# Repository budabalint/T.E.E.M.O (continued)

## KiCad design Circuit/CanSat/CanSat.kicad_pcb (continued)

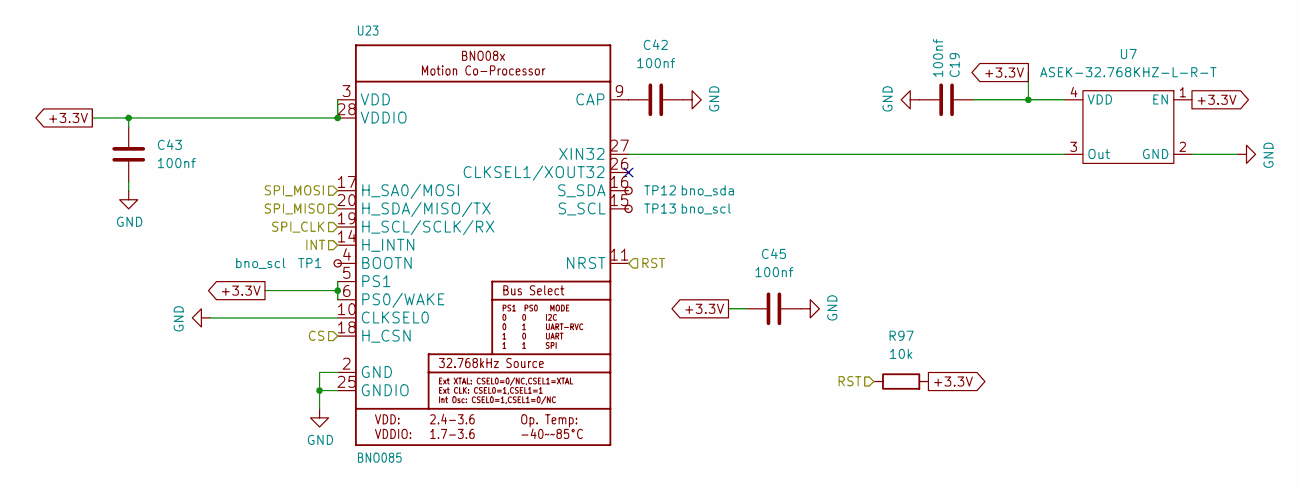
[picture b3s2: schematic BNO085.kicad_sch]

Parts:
C19, C42, C43, C45: 100nf; C_0805_2012Metric
R97: 10k; R_0805_2012Metric
TP1, TP13: bno_scl; TestPoint_Pad_D1.5mm
TP12: bno_sda; TestPoint_Pad_D1.5mm
U7: ASEK-32.768KHZ-L-R-T; Crystal_SMD_3225-4Pin_3.2x2.5mm
U23: BNO085; LGA-28_5.2x3.8mm_P0.5mm

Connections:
+3.3V: C19.1, C43.1, C45.1, R97.2, U7.1 (EN), U7.4 (VDD), U23.3 (VDD), U23.5 (PS1), U23.6 (PS0/WAKE), U23.28 (VDDIO); also elsewhere on the board
/SPI_CLK: U23.19 (H_SCL/SCLK/RX); also elsewhere on the board
/SPI_MISO: U23.20 (H_SDA/MISO/TX); also elsewhere on the board
/SPI_MOSI: U23.17 (H_SA0/MOSI); also elsewhere on the board
/bno_cs: U23.18 (H_CSN); also elsewhere on the board
/bno_int: U23.14 (H_INTN); also elsewhere on the board
/bno_rst: R97.1, U23.11 (NRST); also elsewhere on the board
GND: C19.2, C42.2, C43.2, C45.2, U7.2 (GND), U23.2 (GND), U23.10 (CLKSEL0), U23.25 (GNDIO); also elsewhere on the board
unnamed 75: TP1.1, U23.4 (BOOTN); also elsewhere on the board
unnamed: C42.1, U23.9 (CAP)
unnamed 77: TP13.1, U23.15 (S_SCL); also elsewhere on the board
unnamed 78: TP12.1, U23.16 (S_SDA); also elsewhere on the board
unnamed: U7.3 (Out), U23.27 (XIN32)

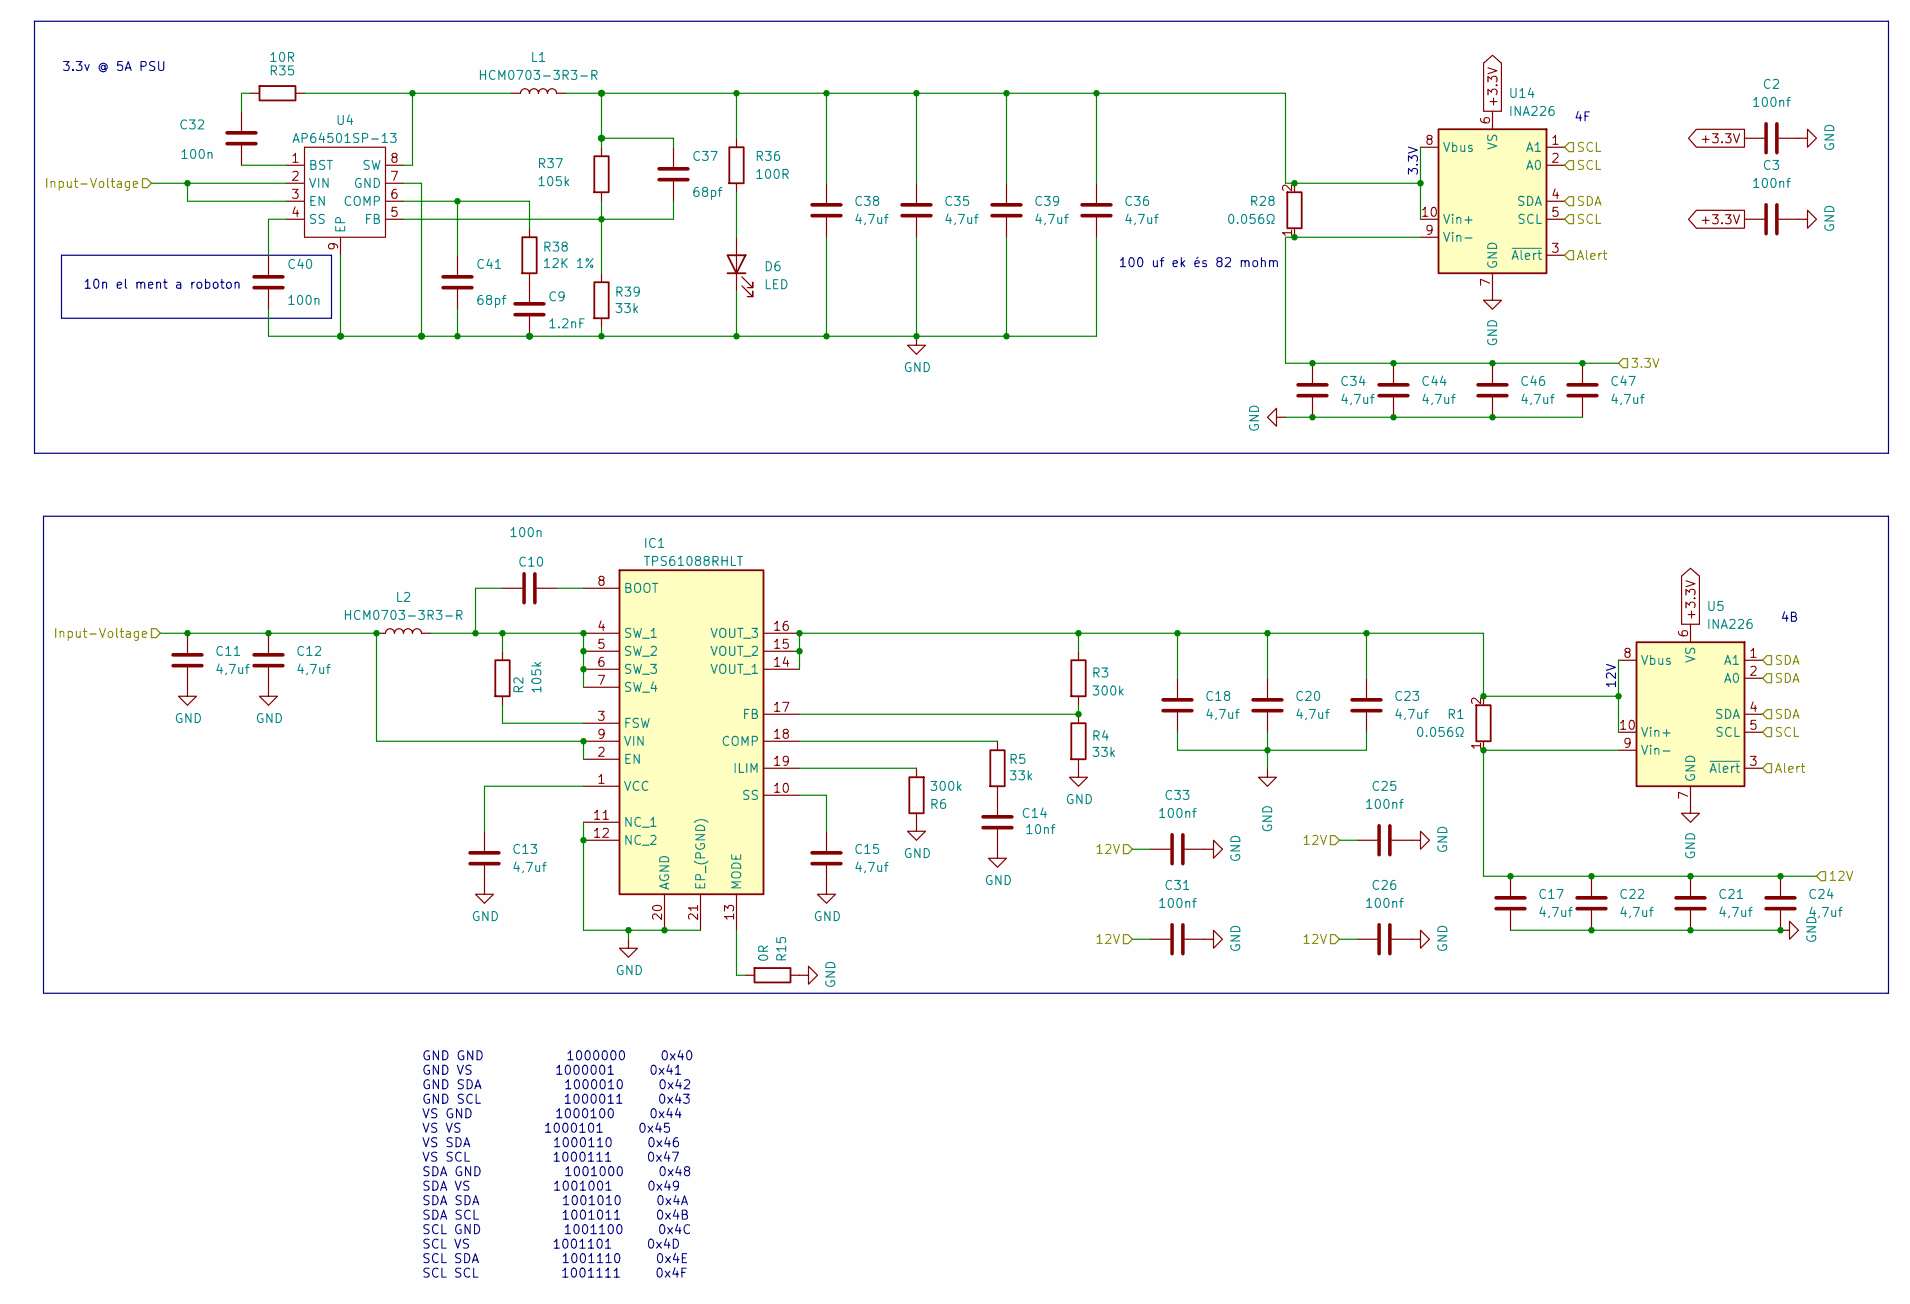
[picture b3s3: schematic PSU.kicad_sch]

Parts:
C2, C3, C25, C26, C31, C33: 100nf; C_0805_2012Metric
C9: 1.2nF; C_0805_2012Metric
C10, C32, C40: 100n; C_0805_2012Metric
C11, C12, C13, C15, C17, C18, C20, C21, C22, C23, C24, C34, C35, C36, C38, C39, C44, C46, C47: 4,7uf; C_0805_2012Metric
C14: 10nf; C_0805_2012Metric
C37, C41: 68pf; C_0805_2012Metric
D6: LED; D_1206_3216Metric
IC1: TPS61088RHLT; BQ24031IRHLRQ1; Manufacturer_Part_Number TPS61088RHLT; Mouser Part Number 595-TPS61088RHLT
L1, L2: HCM0703-3R3-R; HCM1A0805
R1, R28: 0.056Ω; R_1206_3216Metric
R2, R37: 105k; R_0805_2012Metric
R3, R6: 300k; R_0805_2012Metric
R4, R5, R39: 33k; R_0805_2012Metric
R15: 0R; R_0805_2012Metric
R35: 10R; R_0805_2012Metric
R36: 100R; R_0805_2012Metric
R38: 12K 1%; R_0805_2012Metric
U4: AP64501SP-13; SOIC-8-1EP_3.9x4.9mm_P1.27mm_EP2.95x4.9mm_Mask2.71x3.4mm_Th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
U5, U14: INA226; VSSOP-10_3x3mm_P0.5mm

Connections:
+3.3V: C2.1, C3.1, C34.1, C44.1, C46.1, C47.1, R28.1, U5.6 (VS), U14.6 (VS), U14.9 (Vin-); also elsewhere on the board
+12V: C17.1, C21.1, C22.1, C24.1, C25.1, C26.1, C31.1, C33.1, R1.1, U5.9 (Vin-); also elsewhere on the board
/Alert: U5.3 (~Alert), U14.3 (~Alert); also elsewhere on the board
/PSU/Input-Voltage: C11.1, C12.1, IC1.2 (EN), IC1.9 (VIN), L2.2, U4.2 (VIN), U4.3 (EN); also elsewhere on the board
/Slow-SCL: U5.5 (SCL), U14.1 (A1), U14.2 (A0), U14.5 (SCL); also elsewhere on the board
/Slow-SDA: U5.1 (A1), U5.2 (A0), U5.4 (SDA), U14.4 (SDA); also elsewhere on the board
GND: C2.2, C3.2, C9.2, C11.2, C12.2, C13.2, C14.2, C15.2, C17.2, C18.2, C20.2, C21.2, C22.2, C23.2, C24.2, C25.2, C26.2, C31.2, C33.2, C34.2, C35.2, C36.2, C38.2, C39.2, C40.2, C41.2, C44.2, C46.2, C47.2, D6.1 (K), IC1.11 (NC_1), IC1.12 (NC_2), IC1.20 (AGND), IC1.21 (EP_(PGND)), R4.2, R6.1, R15.1, R39.2, U4.7 (GND), U4.9 (EP), U5.7 (GND), U14.7 (GND); also elsewhere on the board
unnamed: C9.1, R38.2
unnamed: C14.1, R5.2
unnamed: C32.1, R35.2
unnamed: D6.2 (A), R36.2
unnamed: C10.2, IC1.8 (BOOT)
unnamed: IC1.18 (COMP), R5.1
unnamed: IC1.17 (FB), R3.2, R4.1
unnamed: IC1.3 (FSW), R2.2
unnamed: IC1.19 (ILIM), R6.2
unnamed: IC1.13 (MODE), R15.2
unnamed: C15.1, IC1.10 (SS)
unnamed: C10.1, IC1.4 (SW_1), IC1.5 (SW_2), IC1.6 (SW_3), IC1.7 (SW_4), L2.1, R2.1
unnamed: C13.1, IC1.1 (VCC)
unnamed: C18.1, C20.1, C23.1, IC1.14 (VOUT_1), IC1.15 (VOUT_2), IC1.16 (VOUT_3), R1.2, R3.1, U5.8 (Vbus), U5.10 (Vin+)
unnamed: C32.2, U4.1 (BST)
unnamed: C41.1, R38.1, U4.6 (COMP)
unnamed: C37.2, R37.2, R39.1, U4.5 (FB)
unnamed: C40.1, U4.4 (SS)
unnamed: L1.1, R35.1, U4.8 (SW)
unnamed: C35.1, C36.1, C37.1, C38.1, C39.1, L1.2, R28.2, R36.1, R37.1, U14.8 (Vbus), U14.10 (Vin+)

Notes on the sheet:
12V
100 uf ek és 82 mohm
10n el ment a roboton
3.3v @ 5A PSU
3.3V
GND GND 1000000 0x40 GND VS 1000001 0x41 GND SDA 1000010 0x42 GND SCL 1000011 0x43 VS GND 1000100 0x44 VS VS 1000101 0x45 VS SDA 1000110 0x46 VS SCL 1000111 0x47 SDA GND 1001000 0x48 SDA VS 1001001 0x49 SDA SDA 1001010 0x4A SDA SCL 1001011 0x4B SCL GND 1001100 0x4C SCL VS 1001101 0x4D SCL SDA 10011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

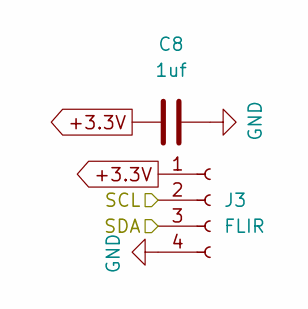
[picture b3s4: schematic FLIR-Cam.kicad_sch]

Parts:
C8: 1uf; C_0805_2012Metric
J3: FLIR; JST_PH_B4B-PH-K_1x04_P2.00mm_Vertical

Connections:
+3.3V: C8.1, J3.1; also elsewhere on the board
/Fast-SCL: J3.2; also elsewhere on the board
/Fast-SDA: J3.3; also elsewhere on the board
GND: C8.2, J3.4; also elsewhere on the board

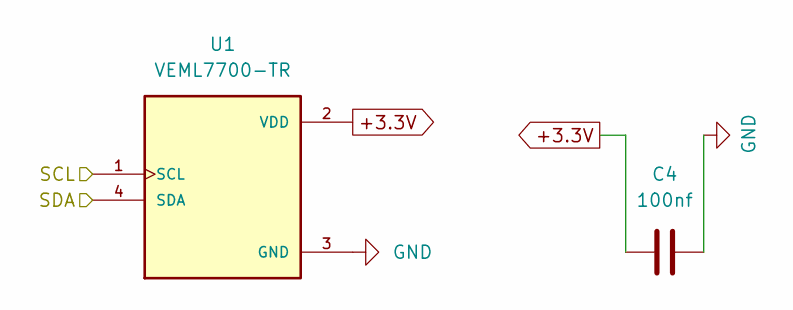
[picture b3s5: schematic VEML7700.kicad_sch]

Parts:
C4: 100nf; C_0805_2012Metric
U1: VEML7700-TR; XDCR_VEML7700-TR; PARTREV 1.6

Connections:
+3.3V: C4.1, U1.2 (VDD); also elsewhere on the board
/Slow-SCL: U1.1 (SCL); also elsewhere on the board
/Slow-SDA: U1.4 (SDA); also elsewhere on the board
GND: C4.2, U1.3 (GND); also elsewhere on the board

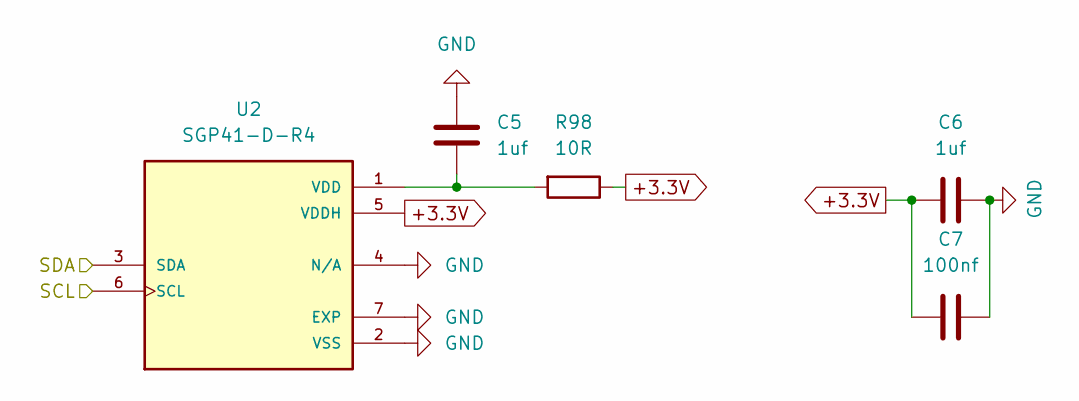
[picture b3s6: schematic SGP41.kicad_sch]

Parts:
C5, C6: 1uf; C_0805_2012Metric
C7: 100nf; C_0805_2012Metric
R98: 10R; R_0805_2012Metric
U2: SGP41-D-R4; XDCR_SGP41-D-R4; PARTREV 1.0

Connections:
+3.3V: C6.1, C7.1, R98.1, U2.5 (VDDH); also elsewhere on the board
/Slow-SCL: U2.6 (SCL); also elsewhere on the board
/Slow-SDA: U2.3 (SDA); also elsewhere on the board
GND: C5.2, C6.2, C7.2, U2.2 (VSS), U2.4 (N/A), U2.7 (EXP); also elsewhere on the board
unnamed: C5.1, R98.2, U2.1 (VDD)

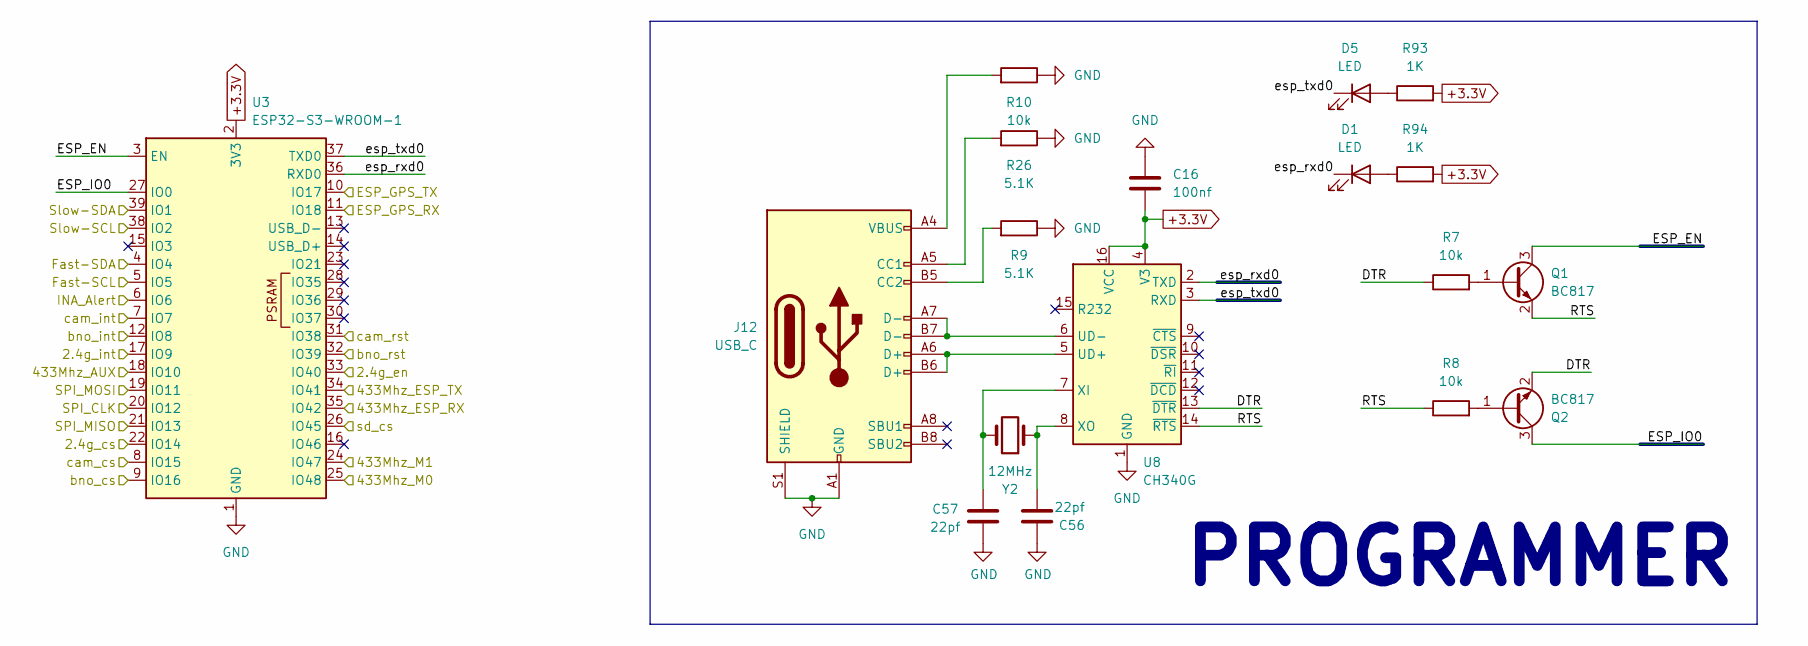
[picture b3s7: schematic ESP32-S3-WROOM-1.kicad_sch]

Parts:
C16: 100nf; C_0805_2012Metric
C56, C57: 22pf; C_0805_2012Metric
D1, D5: LED; D_1206_3216Metric
J12: USB_C; USB_C_Receptacle_Palconn_UTC16-G
Q1, Q2: BC817; SOT-23
R7, R8, R10: 10k; R_0805_2012Metric
R9, R26: 5.1K; R_0805_2012Metric
R93, R94: 1K; R_0805_2012Metric
U3: ESP32-S3-WROOM-1
U8: CH340G; SOIC-16_3.9x9.9mm_P1.27mm
Y2: 12MHz; Crystal_SMD_HC49-SD

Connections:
+3.3V: C16.2, R93.2, R94.2, U3.2 (3V3), U8.4 (V3), U8.16 (VCC); also elsewhere on the board
/2.4g_cs: U3.22 (IO14); also elsewhere on the board
/2.4g_en: U3.33 (IO40); also elsewhere on the board
/2.4g_int: U3.17 (IO9); also elsewhere on the board
/AUX: U3.18 (IO10); also elsewhere on the board
/Alert: U3.6 (IO6); also elsewhere on the board
/ESP32-S3-WROOM-1/DTR: Q2.2 (E), R7.1, U8.13 (~DTR)
/ESP32-S3-WROOM-1/ESP_EN: Q1.3 (C), U3.3 (EN)
/ESP32-S3-WROOM-1/ESP_IO0: Q2.3 (C), U3.27 (IO0)
/ESP32-S3-WROOM-1/RTS: Q1.2 (E), R8.1, U8.14 (~RTS)
/ESP32-S3-WROOM-1/esp_rxd0: D1.1 (K), U3.36 (RXD0), U8.2 (TXD)
/ESP32-S3-WROOM-1/esp_txd0: D5.1 (K), U3.37 (TXD0), U8.3 (RXD)
/Fast-SCL: U3.5 (IO5); also elsewhere on the board
/Fast-SDA: U3.4 (IO4); also elsewhere on the board
/GPS_RX: U3.10 (IO17); also elsewhere on the board
/GPS_TX: U3.11 (IO18); also elsewhere on the board
/M0: U3.25 (IO48); also elsewhere on the board
/M1: U3.24 (IO47); also elsewhere on the board
/RX: U3.34 (IO41); also elsewhere on the board
/SPI_CLK: U3.20 (IO12); also elsewhere on the board
/SPI_MISO: U3.21 (IO13); also elsewhere on the board
/SPI_MOSI: U3.19 (IO11); also elsewhere on the board
/Slow-SCL: U3.38 (IO2); also elsewhere on the board
/Slow-SDA: U3.39 (IO1); also elsewhere on the board
/TX: U3.35 (IO42); also elsewhere on the board
/bno_cs: U3.9 (IO16); also elsewhere on the board
/bno_int: U3.12 (IO8); also elsewhere on the board
/bno_rst: U3.32 (IO39); also elsewhere on the board
/cam_cs: U3.8 (IO15); also elsewhere on the board
/cam_int: U3.7 (IO7); also elsewhere on the board
/cam_rst: U3.31 (IO38); also elsewhere on the board
/sd_cs: U3.26 (IO45); also elsewhere on the board
GND: C16.1, C56.2, C57.2, J12.A1 (GND), J12.A12 (GND), J12.B1 (GND), J12.B12 (GND), J12.S1 (SHIELD), R9.1, R10.1, R26.1, U3.1 (GND), U3.40 (GND), U3.41 (GND), U8.1 (GND); also elsewhere on the board
unnamed: D1.2 (A), R94.1
unnamed: D5.2 (A), R93.1
unnamed: J12.A5 (CC1), R26.2
unnamed: J12.B5 (CC2), R9.2
unnamed: J12.A4 (VBUS), J12.A9 (VBUS), J12.B4 (VBUS), J12.B9 (VBUS), R10.2
unnamed: Q1.1 (B), R7.2
unnamed: Q2.1 (B), R8.2
unnamed: J12.A6 (D+), J12.B6 (D+), U8.5 (UD+)
unnamed: J12.A7 (D-), J12.B7 (D-), U8.6 (UD-)
unnamed: C57.1, U8.7 (XI), Y2.2
unnamed: C56.1, U8.8 (XO), Y2.1

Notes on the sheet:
PROGRAMMER

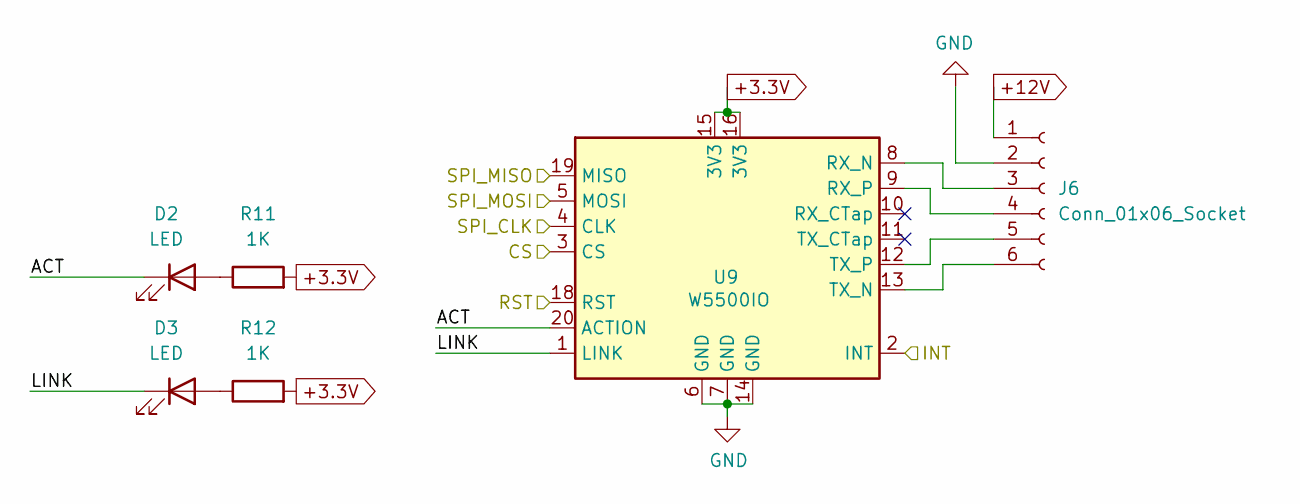
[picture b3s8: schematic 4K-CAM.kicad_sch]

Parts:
D2, D3: LED; D_1206_3216Metric
J6: Conn_01x06_Socket; JST_PH_B6B-PH-K_1x06_P2.00mm_Vertical
R11, R12: 1K; R_0805_2012Metric
U9: W5500IO; W5500-io

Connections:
+3.3V: R11.2, R12.2, U9.15 (3V3), U9.16 (3V3); also elsewhere on the board
+12V: J6.1; also elsewhere on the board
/4K-CAM/ACT: D2.1 (K), U9.20 (ACTION)
/4K-CAM/LINK: D3.1 (K), U9.1 (LINK)
/SPI_CLK: U9.4 (CLK); also elsewhere on the board
/SPI_MISO: U9.19 (MISO); also elsewhere on the board
/SPI_MOSI: U9.5 (MOSI); also elsewhere on the board
/cam_cs: U9.3 (CS); also elsewhere on the board
/cam_int: U9.2 (INT); also elsewhere on the board
/cam_rst: U9.18 (RST); also elsewhere on the board
GND: J6.2, U9.6 (GND), U9.7 (GND), U9.14 (GND); also elsewhere on the board
unnamed: D2.2 (A), R11.1
unnamed: D3.2 (A), R12.1
unnamed: J6.3, U9.8 (RX_N)
unnamed: J6.4, U9.9 (RX_P)
unnamed: J6.5, U9.12 (TX_P)
unnamed: J6.6, U9.13 (TX_N)

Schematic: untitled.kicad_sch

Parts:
C1: 100nf; C_0805_2012Metric
U21: BME280; Bosch_LGA-8_2.5x2.5mm_P0.65mm_ClockwisePinNumbering

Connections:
+3.3V: C1.1, U21.2 (CSB), U21.5 (SDO), U21.6 (VDDIO), U21.8 (VDD); also elsewhere on the board
/Slow-SCL: U21.4 (SCK); also elsewhere on the board
/Slow-SDA: U21.3 (SDI); also elsewhere on the board
GND: C1.2, U21.1 (GND), U21.7 (GND); also elsewhere on the board

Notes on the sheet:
0x77 @ VDD 0x76 @ GND

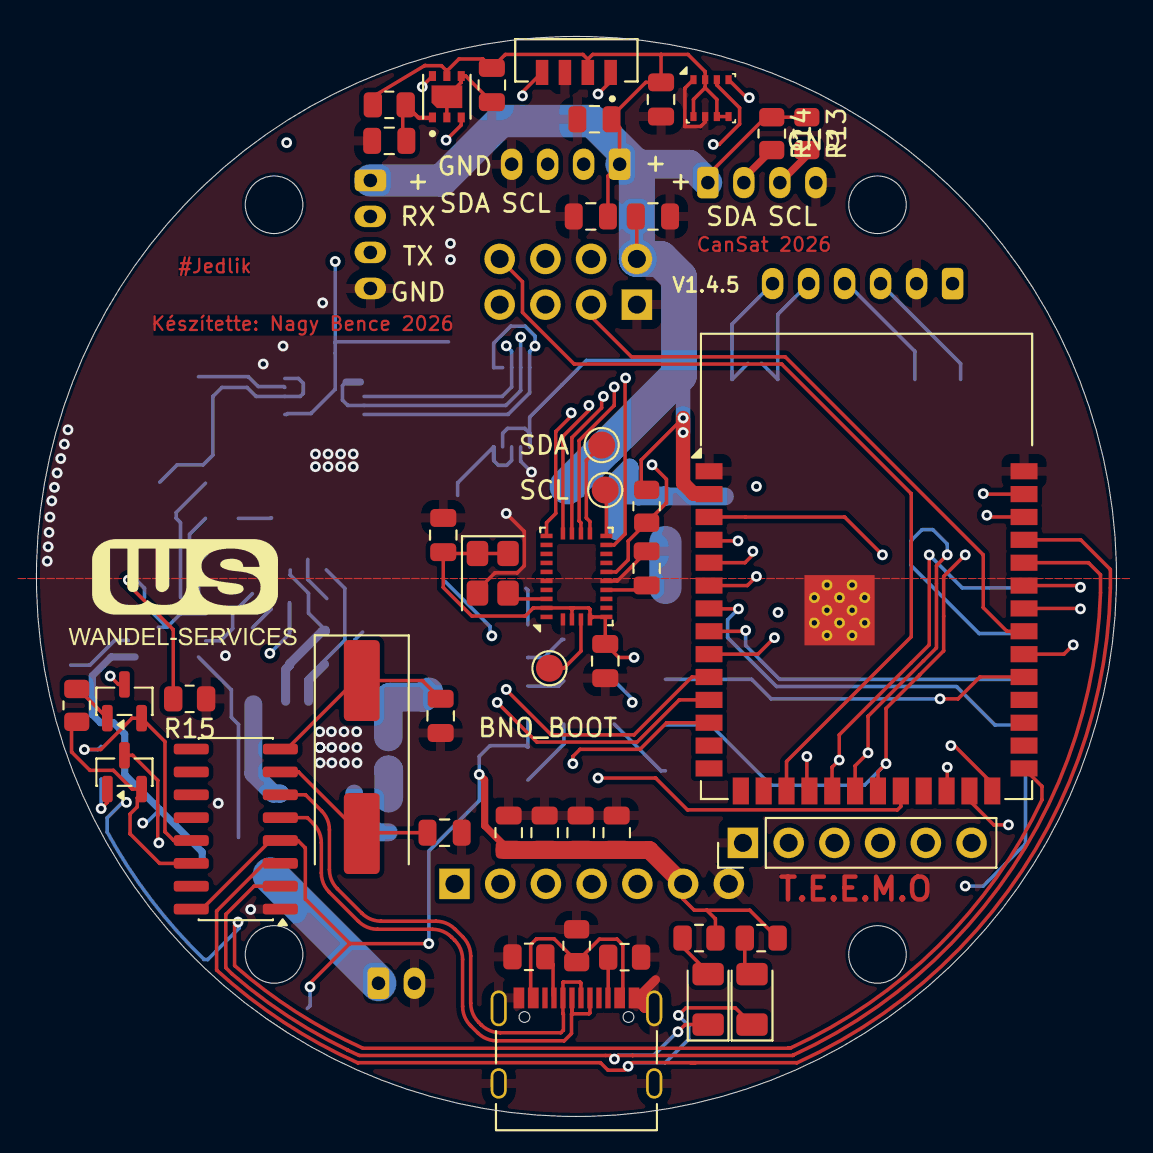
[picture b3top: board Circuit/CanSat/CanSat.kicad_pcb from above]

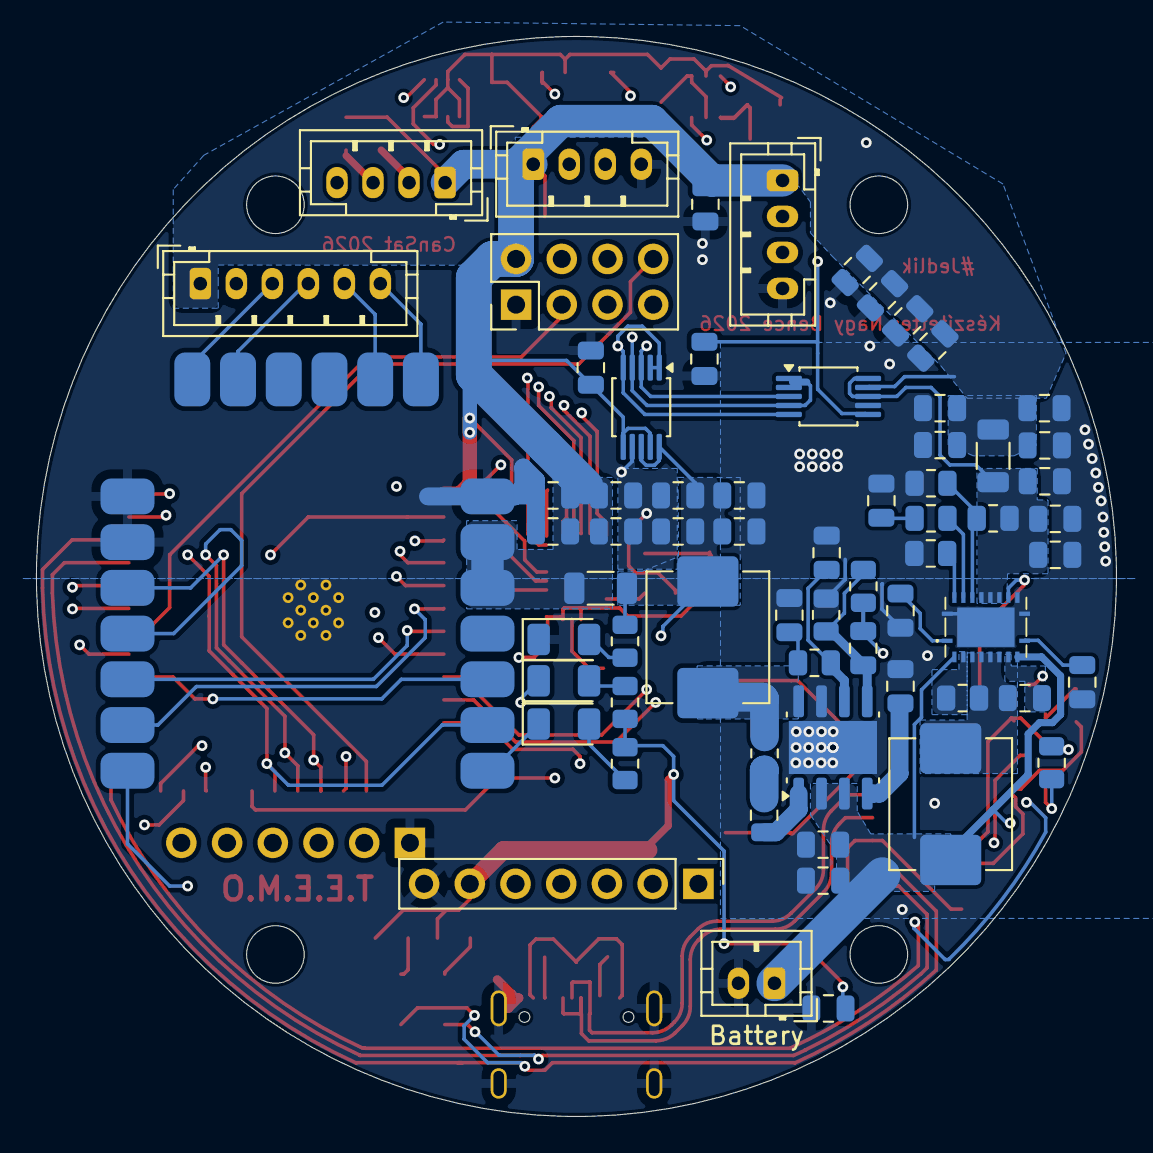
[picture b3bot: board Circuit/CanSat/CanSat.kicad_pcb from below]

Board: 4 copper layers, 60.0 x 60.0 mm, 109 parts (66 on the bottom side), 80 nets.

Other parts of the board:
BNO_BOOT: bno_scl; TestPoint_Pad_D1.5mm
Battery: Conn_01x02_Socket; JST_PH_B2B-PH-K_1x02_P2.00mm_Vertical
C27, C28, C29, C30: 4,7uf; C_0805_2012Metric
SCL: bno_scl; TestPoint_Pad_D1.5mm
SDA: bno_sda; TestPoint_Pad_D1.5mm

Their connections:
+3.3V: C27.1, C28.1, C29.1, C30.1; also elsewhere on the board
/PSU/Input-Voltage: Battery.1; also elsewhere on the board
GND: Battery.2, C27.2, C28.2, C29.2, C30.2; also elsewhere on the board
unnamed 75: BNO_BOOT.1; also elsewhere on the board
unnamed 77: SCL.1; also elsewhere on the board
unnamed 78: SDA.1; also elsewhere on the board

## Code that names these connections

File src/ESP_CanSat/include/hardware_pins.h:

#pragma once
#include <Arduino.h>

const int Sensor_SPI_MOSI = 11;
const int Sensor_SPI_MISO = 13;
const int Sensor_SPI_SCL = 12;

const uint8_t BNO_CS = 16;
//const uint8_t RADIO_24GHZ_CS = 14;
const uint8_t SD_CARD_CS = 45; //45
const uint8_t CAM_CS = 15;


const uint8_t SENSOR_I2C_SDA = 1;
const uint8_t SENSOR_I2C_SCL = 2;

const uint8_t THERMAL_CAM_I2C_SDA = 4;
const uint8_t THERMAL_CAM_I2C_SCL = 5;

const uint8_t RADIO_TX = 42; //42
const uint8_t RADIO_RX = 41; //41
const uint8_t GPS_TX = 17;
const uint8_t GPS_RX = 18;

const int BNO_INT = 8;
const uint8_t CAM_INT = 7;
//const uint8_t RADIO_24GHZ_INT = 9;

const int BNO_RST = 39;
const uint8_t CAM_RST = 38;
//const uint8_t RADIO_24GHZ_EN = 40;

const uint8_t RADIO_433MHZ_M1 = 47; //47
const uint8_t RADIO_433MHZ_M0 = 48; //48
const uint8_t RADIO_AUX = 10; //10



const uint8_t SX1280_NSS  =  14;
const uint8_t SX1280_DIO1 =  6;
const uint8_t SX1280_NRST =  40;
const uint8_t SX1280_BUSY =  9;

const uint8_t CAM_POWER_PIN  =  16;

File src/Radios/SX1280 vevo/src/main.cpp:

/*
 * ESP32-S3 VEVŐ (Receiver) - SX1280 + OLED + NeoPixel LED
 * SX1280 rádión fogadja a 126 bájtos adatcsomagokat,
 * hozzáfűzi az RSSI-t, továbbítja 127 bájtként a soros porton,
 * és kezeli az OLED kijelzőt, illetve a WS2812B LED sort a jelerősség alapján.
 */

#include <RadioLib.h>
#include <SPI.h>
#include <Wire.h>
#include <Adafruit_GFX.h>
#include <Adafruit_SSD1306.h>
#include <Adafruit_NeoPixel.h>

// --- SX1280 PINOK ---
#define SPI_SCK       12
#define SPI_MOSI      11
#define SPI_MISO      9
#define SX1280_NSS    14
#define SX1280_DIO1   20
#define SX1280_NRST   40
#define SX1280_BUSY   13

SPIClass customSPI(FSPI);
Module* module = new Module(SX1280_NSS, SX1280_DIO1, SX1280_NRST, SX1280_BUSY, customSPI);
SX1280 radio(module);

#define PACKET_LEN 126
#define SERIAL_LEN 127
#define SYNC_BYTE  0xFE
#define RSSI_UPDATE_INTERVAL 50

uint8_t videoPacket[PACKET_LEN];
volatile bool receivedFlag = false;

// --- OLED ÉS LED PINOK ÉS BEÁLLÍTÁSOK ---
const uint8_t SDA_PIN = 21;
const uint8_t SCL_PIN = 47;

#define LED_COUNT   8
#define LED_PIN     48

#define SCREEN_WIDTH 128
#define SCREEN_HEIGHT 64

#define OLED_RESET     -1
#define SCREEN_ADDRESS 0x3C

Adafruit_NeoPixel strip(LED_COUNT, LED_PIN, NEO_GRB + NEO_KHZ800);
Adafruit_SSD1306 display(SCREEN_WIDTH, SCREEN_HEIGHT, &Wire, OLED_RESET);

// --- STATISZTIKA ÉS RSSI VÁLTOZÓK ---
uint32_t totalPackets = 0;        // Ez volt a packetCounter
unsigned long crcErrors = 0;
int8_t lastRssi = 0;              // cache-elt utolsó RSSI érték

unsigned long lastSignalTime = 0;
const unsigned long signalTimeout = 1000;

// CRC-8 Kalkulátor
uint8_t calcCrc8(const uint8_t *data, size_t len) {
  uint8_t crc = 0x00;
    while (len--) {
        uint8_t extract = *data++;
        for (uint8_t tempI = 8; tempI; tempI--) {
            uint8_t sum = (crc ^ extract) & 0x01;
            crc >>= 1;
            if (sum) {
                crc ^= 0x8C;
            }
            extract >>= 1;
        }
    }
    return crc;
}

#if defined(ESP8266) || defined(ESP32)
  IRAM_ATTR
#endif
void setFlag(void) {
  receivedFlag = true;
}

void setupRadio() {
  Serial.println("--- SX1280 Inicializalasa folyamatban... ---");
  
  int state = radio.beginFLRC(2485.0, 1300, 2, 0, 16, RADIOLIB_SHAPING_0_5);
  
  if (state != RADIOLIB_ERR_NONE) {
    Serial.print("Hiba az inicializalas soran! Hibakod: ");
    Serial.println(state);
    while (1); // Itt megáll a program, ha hiba van
  }
  
  Serial.println("--- SX1280 Sikeresen inicializalva! Varas az adatokra... ---");

  uint8_t syncWord[] = { 0xC1, 0xA2, 0xB3, 0xD4 };
  radio.setSyncWord(syncWord, 4);
  radio.setCRC(2); 

  radio.fixedPacketLengthMode(PACKET_LEN);
  radio.setHighSensitivityMode(true);
  radio.setDio1Action(setFlag);

  radio.startReceive();
}

void setup() {
  Serial.begin(921600);
  delay(100);

  // --- OLED ÉS LED INICIALIZÁLÁSA ---
  Wire.begin(SDA_PIN, SCL_PIN);

  if(!display.begin(SSD1306_SWITCHCAPVCC, SCREEN_ADDRESS)) {
    Serial.println("OLED init hiba");
    while(true);
  }

  display.clearDisplay();
  display.setTextSize(2); 
  display.setTextColor(SSD1306_WHITE);
  display.setCursor(0,20);
  display.print("Indulas...");
  display.display();

  delay(200);
  strip.begin();
  delay(500);
  strip.setPixelColor(6, 0, 255, 255);
  strip.show();
  delay(500);
  // ------------------------------------

  customSPI.begin(SPI_SCK, SPI_MISO, SPI_MOSI, -1);
  setupRadio();
  
  display.clearDisplay();
  display.setCursor(0, 20);
  display.print("Vetelre kesz");
  display.display();
}

void loop() {
  // Statikus változók a kijelző és LED logikához
  static int lastNumLeds = -1;
  static uint32_t lastColor = 0;
  static bool hasSignal = false;
  static int displayUpdateCount = 0;

  if (receivedFlag) {
    receivedFlag = false;

    int state = radio.readData(videoPacket, PACKET_LEN);
    lastSignalTime = millis(); // Bejövő jel időbélyege (No Signal detektáláshoz)

    bool packetOk = false;
    if (state == RADIOLIB_ERR_NONE && videoPacket[0] == SYNC_BYTE) {
      uint8_t crcCalc = calcCrc8(videoPacket, PACKET_LEN - 1);
      uint8_t crcRecv = videoPacket[PACKET_LEN - 1];
      packetOk = (crcCalc == crcRecv);
    }

    if (!packetOk) {
      crcErrors++; // Ha hibás a csomag (CRC vagy más hiba)
    } else {
      totalPackets++;
      if (totalPackets % RSSI_UPDATE_INTERVAL == 0) {
        // FONTOS: még startReceive() ELŐTT kell lekérni, különben a chip törli a regisztert!
        float rawRssi = radio.getRSSI();
        int rssiInt = (int)rawRssi;
        if (rssiInt > 0)    rssiInt = 0;
        if (rssiInt < -127) rssiInt = -127;
        lastRssi = (int8_t)rssiInt;
      }
    }

    // Csak EZUTÁN indítjuk újra a vételt (A legfontosabb sebesség optimalizáció marad)
    radio.startReceive();

    if (packetOk) {
      // 1. SOROS PORTI KIKÜLDÉS (Azonnal továbbítjuk PC felé, nincs késedelem)
      uint8_t rssiByte = (uint8_t)(-lastRssi);
      uint8_t outBuffer[SERIAL_LEN];
      memcpy(outBuffer, videoPacket, PACKET_LEN);
      outBuffer[PACKET_LEN] = (255 - rssiByte);

      Serial.write(outBuffer, SERIAL_LEN);

      // 2. LED ÉS OLED KIJELZŐ FRISSÍTÉSE (Csak miután az adat már ment a Serial-on)
      int rssi_dbm = (int)lastRssi;

      int numLedsOn = 1;
      uint32_t color = 0;

      int calc_rssi = constrain(rssi_dbm, -91, 0);
      if (calc_rssi <= -62) {
        color = strip.Color(255, 0, 0);
        numLedsOn = map(calc_rssi, -91, -62, 1, 8);
      } 
      else if (calc_rssi <= -32) {
        color = strip.Color(255, 255, 0);
        numLedsOn = map(calc_rssi, -61, -32, 1, 8);
      } 
      else {
        color = strip.Color(0, 255, 0);
        numLedsOn = map(calc_rssi, -31, 0, 1, 8);
      }
      numLedsOn = constrain(numLedsOn, 1, 8);

      if (numLedsOn != lastNumLeds || color != lastColor || !hasSignal) {
        strip.clear();
        for (int i = 0; i < numLedsOn; i++) {
          strip.setPixelColor(i, color);
        }
        strip.show();
        
        lastNumLeds = numLedsOn; 
        lastColor = color;
        hasSignal = true;        
      }

      // --- OLED Kijelző frissítése (Minden 5. jó csomagnál, ahogy kérted) ---
      if (displayUpdateCount >= 5) {
        display.clearDisplay();
        
        display.setTextSize(2);
        display.setCursor(0, 0);
        display.print("RSSI:");
        display.print(rssi_dbm);

        display.setTextSize(1);
        display.setCursor(0, 30);
        display.print("Csomagok : ");
        display.print(totalPackets);

        display.setCursor(0, 45);
        display.print("CRC Hiba : ");
        display.print(crcErrors);

        display.display();
        displayUpdateCount = 0;
      }
      displayUpdateCount++;
    }
  } 
  else {
    // --- JEL MEGSZAKADÁS DETEKTÁLÁSA (No Signal) ---
    if (millis() - lastSignalTime >= signalTimeout) {
      if (hasSignal) {
        display.clearDisplay();
        display.setTextSize(2); 
        display.setCursor(0, 20);
        display.print("No Signal!");
        display.display();

        strip.clear();
        for (int i = 0; i < LED_COUNT; i++) {
          strip.setPixelColor(i, 255, 0, 0);
        }
        strip.show();

        hasSignal = false; 
        lastNumLeds = -1;  
        lastColor = 0;
      }
    }
  }
}

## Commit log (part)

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2025-11-27 backut commit first version of panel
2026-01-09 pcb last before finish
2026-01-09 Main code sensors first try
2026-01-10 pcb update
2026-01-10 all sensors work
2026-01-10 sensor package assembly complete
2026-01-10 kicad update
2026-01-10 Thermal Camera files added
2026-01-11 Thermal Camera packet building
2026-01-11 Thermal Cam debuging
2026-01-12 camera I2C bug fixed
2026-01-12 Sensor readtime optimalization
2026-01-13 All packet bug fixed
2026-01-14 SD first try
2026-01-22 sd_card_shared_spi
2026-01-22 SD_Card_in_oop
2026-01-22 433Mhz
2026-01-23 433 Mhz radio code fixed
2026-01-23 433Mhz radio oop code
2026-01-24 thread management started
2026-01-25 thread management
2026-01-26 Thread mangae debuging
2026-01-27 Thermal cam I2c buffer bug fixed
2026-01-28 Uart radio bug fixed
2026-01-29 refactored config
2026-02-02 w5500 and first code on the pcb
2026-02-02 ina226 code
2026-02-03 Ina sensor bug fixed
2026-02-05 All sensor works on the pcb
2026-02-07 the 433 mhz radio and all sensors are working and the ground station receives the data
2026-02-08 2.4 Ghz radio
2026-02-09 2.4 Ghz radio oop code
2026-02-10 2.4Ghz radio debuging
2026-02-10 Main cam class
2026-02-20 ground station code
2026-02-20 gnd station 433 code finished
2026-02-21 packet bug and ground station code fixed
2026-02-22 radio speed debuging
2026-02-26 2.4Ghz radio Setup
2026-03-03 lora debuging
2026-03-10 sensors init bug fixed
2026-03-10 2.4G radio libary lib deps
2026-03-11 grid rotater
2026-03-11 grid rotater with simulated koordinates
2026-03-11 SD write but bno is an idiot
2026-03-12 bno egy fos
2026-03-12 bno and sd spi debuging
2026-03-13 bno I2C
2026-03-13 bno I2c sd bug finaly fixed
2026-03-14 sd writing finished
2026-03-16 Implement SetPinModes function in CanSat
    Added SetPinModes function to initialize pin modes for various components.
2026-03-16 Add SetPinModes method declaration to CanSat class
2026-03-16 w5500 good code
2026-03-20 Refactor motor control logic for yaw and pitch
2026-03-23 grid rotator debug code
2026-03-23 grid rotater debuging
2026-03-23 drid rotater code bug fixing
2026-03-24 grid rotater working code with manual buttons
2026-03-25 grid rotater uart commands
2026-03-25 hfdgh
2026-03-26 sx1280 rrx tx code
2026-03-27 adc values for manual mode
2026-04-26 latest pcb, sx module, initial new sensor panel
2026-06-30 grid rotater bug fixing
